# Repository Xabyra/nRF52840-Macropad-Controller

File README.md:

# nRF52840 Custom Wireless Macropad

An end-to-end open-source wireless macropad built on top of the **Nordic nRF52840** SoC. The system features custom hardware design, **Zephyr RTOS** multi-threaded firmware, and a dedicated **Flutter** desktop companion application for cross-platform configuration.

---

## ⚡ Key Highlights

* **Nordic nRF52840 SoC**: BLE HID keyboard & mouse profiles with low-power optimizations.
* **Dual Layer Architecture**: Full-featured matrix scanning + rotary encoder control.
* **Zephyr RTOS Engine**: Event-driven multitasking, hardware-accelerated BLE stack, and flash settings storage.
* **Companion App**: Cross-platform desktop GUI (Windows/Linux) built with Flutter for live keymap reassignment and sequence management.
* **Custom PCB**: Designed from schematic through routed 2-layer PCB and STEP model using KiCad.

---

## 🛠️ System Overview

### 1. Hardware Design (KiCad)
Custom schematic and 2-layer PCB layout developed in KiCad, optimized for Nordic nRF52-series wireless routing and mechanical switch integration.

* KiCad project source files and the STEP model are located in the [`/Hardware`](./Hardware) directory.

---

### 2. Firmware (Zephyr RTOS / C++)
Event-driven embedded architecture leveraging modern RTOS primitives:
* **Key Matrix Scanner**: Hardware debounce and rapid matrix polling.
* **Encoder Handler**: Hardware quadrature decoding with acceleration.
* **BLE HID Profile**: Seamless connectivity and automatic reconnect routine.
* **Power Management**: Aggressive sleep and system-off modes for prolonged battery endurance.

Source code and build instructions are located in the [`/Firmware`](./Firmware) directory.

---

### 3. Desktop Software (Flutter)
A responsive desktop application for live parameter synchronization over BLE:

* Intuitive matrix binding and layer configuration.
* Macro sequence editor with custom delays.
* Real-time battery status and profile switcher.

Source code and setup instructions are located in the [`/Software`](./Software) directory.

---

## 📂 Repository Structure

```text
├── Hardware/   # KiCad schematic, PCB layout, and STEP model
├── Firmware/   # Zephyr RTOS source code, devicetree overlays, prj.conf
├── Software/   # Flutter configuration application source
└── docs/       # Media, hardware photos, and diagrams
```

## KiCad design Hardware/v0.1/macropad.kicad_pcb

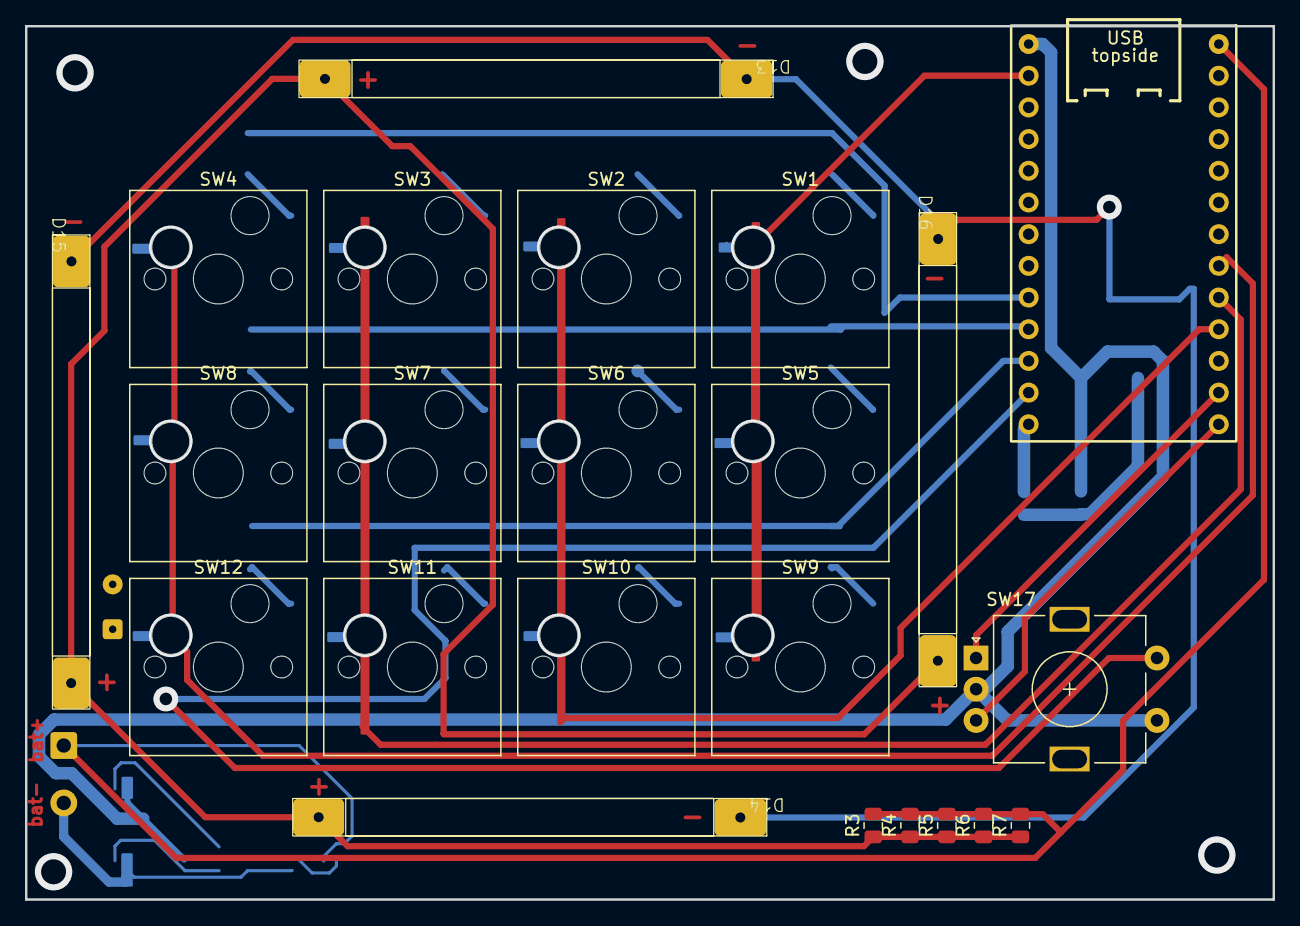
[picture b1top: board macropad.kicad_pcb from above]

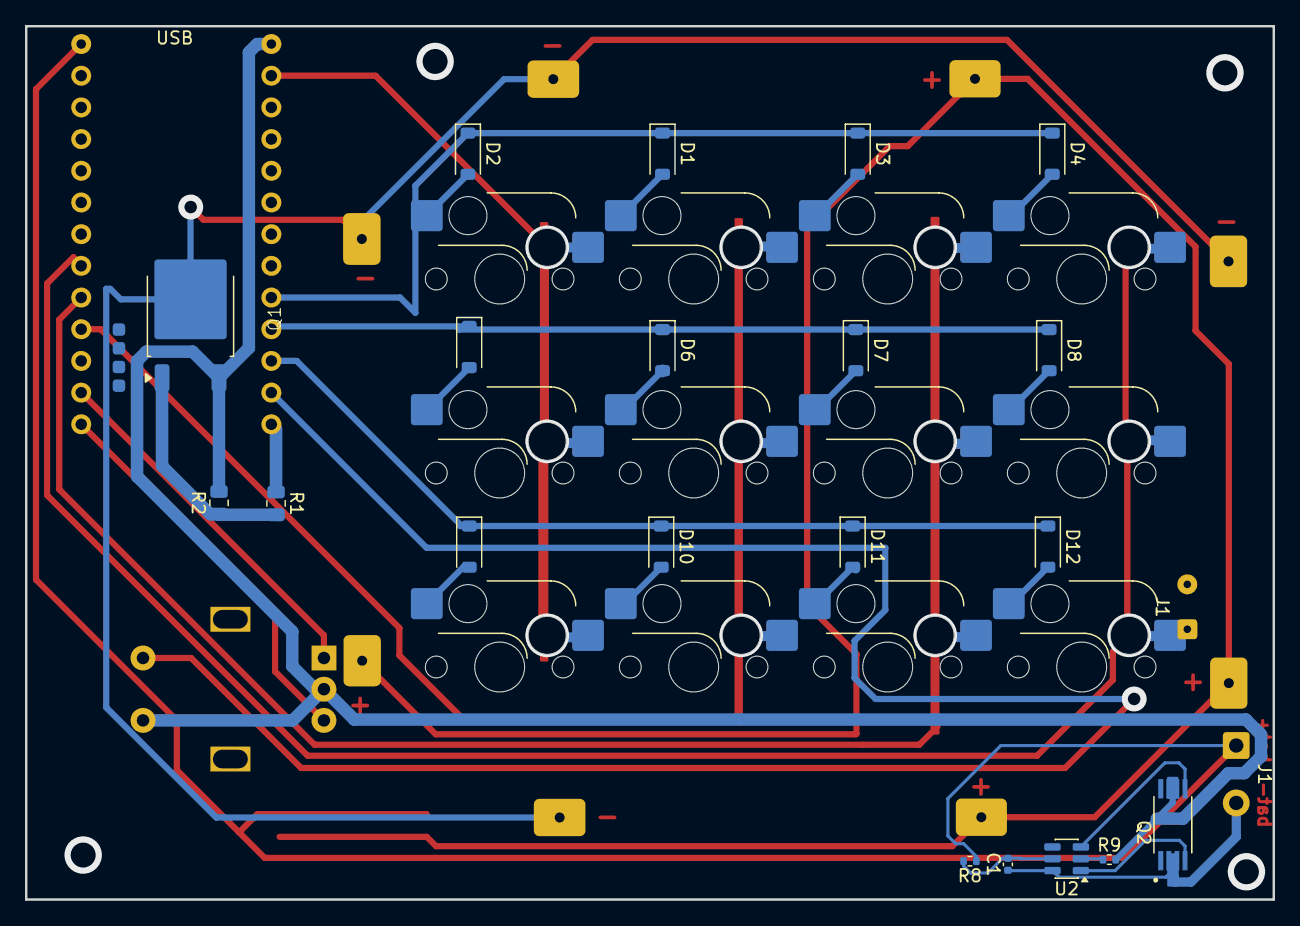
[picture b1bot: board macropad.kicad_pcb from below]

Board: 2 copper layers, 100.0 x 70.0 mm, 45 parts (22 on the bottom side), 33 nets.

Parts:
C1: 0.1u; C_0402_1005Metric
D1, D2, D3, D4, D5, D6, D7, D8, D9, D10, D11, D12: 1N4148W; D_SOD-123
D13, D14, D15, D16: LED; Led38mm
J1: Conn_01x02_Pin; SolderWire-0.1sqmm_1x02_P3.6mm_D0.4mm_OD1mm
J1#2: Conn_01x02_Pin; SolderWire-0.5sqmm_1x02_P4.6mm_D0.9mm_OD2.1mm
Q1: NMOS; p0903bdg
Q2: FS8205A; SOP65P640X120-8N
R1, R3, R4, R5, R6, R7: 330; R_0805_2012Metric
R2: 47k; R_0805_2012Metric
R8: 100; R_0402_1005Metric
R9: 1k; R_0402_1005Metric
SW1, SW2, SW3, SW4, SW5, SW6, SW7, SW8, SW9, SW10, SW11, SW12: SW_Push; SW_Hotswap_Kailh_MX_1.00u
SW17: RotaryEncoder_Switch; RotaryEncoder_Alps_EC11E-Switch_Vertical_H20mm
U1: SuperMini NRF52840
U2: DW01A; SOT-23-6

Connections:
/from_led_to_grd: D13.1 (K), D14.1 (K), D15.1 (K), D16.1 (K), Q1.1 (D)
GND: Q1.3 (S), Q2.6, Q2.7, R2.2, R9.2, SW17.C, SW17.S1, U1.28 (GND)
unnamed: D1.2 (A), SW2.2
unnamed: D1.1 (K), D2.1 (K), D3.1 (K), D4.1 (K), U1.8 (D5)
unnamed: D2.2 (A), SW1.2
unnamed: D3.2 (A), SW3.2
unnamed: D4.2 (A), SW4.2
unnamed: D5.2 (A), SW5.2
unnamed: D5.1 (K), D6.1 (K), D7.1 (K), D8.1 (K), U1.9 (D6)
unnamed: D6.2 (A), SW6.2
unnamed: D7.2 (A), SW7.2
unnamed: D8.2 (A), SW8.2
unnamed: D9.2 (A), SW9.2
unnamed: D10.2 (A), SW10.2
unnamed: D9.1 (K), D10.1 (K), D11.1 (K), D12.1 (K), U1.10 (D7)
unnamed: D11.2 (A), SW11.2
unnamed: D12.2 (A), SW12.2
unnamed: D13.2 (A), D14.2 (A), D15.2 (A), D16.2 (A), R3.1, R4.1, R5.1, R6.1, R7.1
unnamed: Q1.2 (G), R1.2, R2.1
unnamed: SW1.1, SW5.1, SW9.1, U1.1 (D1)
unnamed: SW17.S2, U1.11 (D8)
unnamed: R1.1, U1.12 (D9)
unnamed: SW17.B, U1.24 (D10)
unnamed: SW2.1, SW6.1, SW10.1, U1.21 (D15)
unnamed: SW17.A, U1.23 (D16)
unnamed: SW3.1, SW7.1, SW11.1, U1.20 (D18)
unnamed: SW4.1, SW8.1, SW12.1, U1.19 (D19)
unnamed: R9.1, U2.2 (CS)
unnamed: Q2.5, U2.3 (OC)
unnamed: Q2.4, U2.1 (OD)
unnamed: C1.2, R8.2, U2.5 (VCC)
P+: J1#2.1, R3.2, R4.2, R5.2, R6.2, R7.2, R8.1, U1.29 (Bat+)
Vbat-: C1.1, J1#2.2, Q2.2, Q2.3, U2.6 (GND)
